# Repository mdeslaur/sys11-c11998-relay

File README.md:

# Williams System 11 24v Relay board

This is a replacement 24v relay board for use in Williams System 11
pinball machines. The original part number is C-11998-1.

It is in KiCad 7 format.

The gerbers for JLCPCB are in the zip file in the gerbers directory.

This has not been tested yet. Version 1.0 of this design will be tested
soon in a Williams Diner.

Change history:  
1.0 - Initial version  

To Do:  
- Clean up the schematic.  

Marc Deslauriers
2024-01-16

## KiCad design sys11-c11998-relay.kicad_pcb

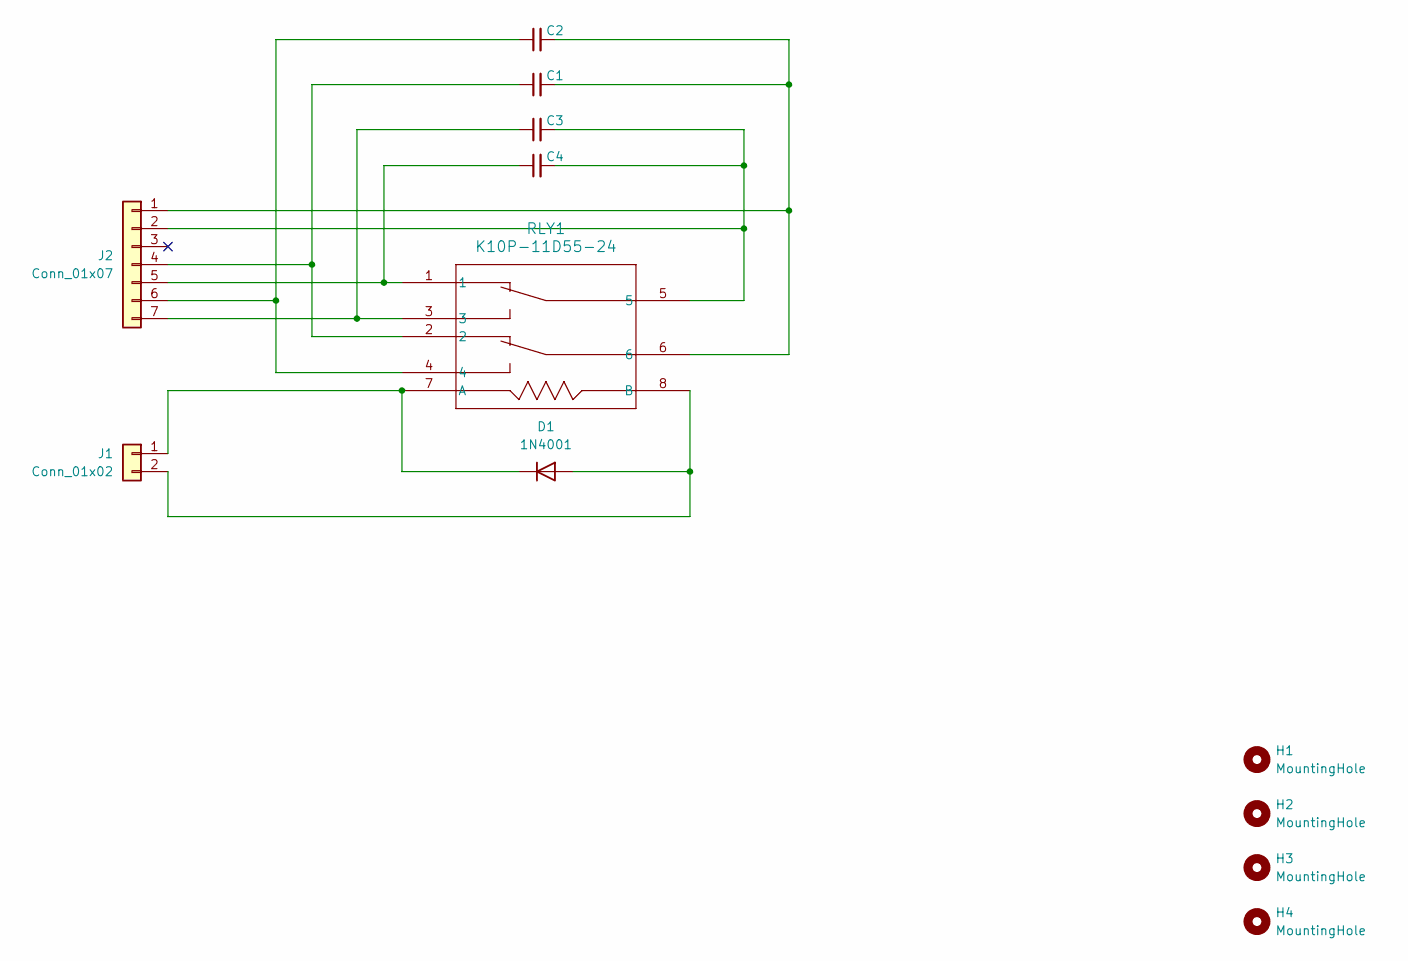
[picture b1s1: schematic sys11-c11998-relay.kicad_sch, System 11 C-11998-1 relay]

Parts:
C1, C2, C3, C4: Unpopulated; C_Axial_L3.8mm_D2.6mm_P10.00mm_Horizontal
D1: 1N4001; D_DO-41_SOD81_P12.70mm_Horizontal
H1, H2, H3, H4: MountingHole; MountingHole_3.2mm_M3
J1: Conn_01x02; Molex_KK-396_5273-02A_1x02_P3.96mm_Vertical_mod
J2: Conn_01x07; Molex_KK-396_5273-07A_1x07_P3.96mm_Vertical_mod
RLY1: K10P-11D55-24

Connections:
unnamed: D1.2 (A), J1.2, RLY1.8 (B)
unnamed: D1.1 (K), J1.1, RLY1.7 (A)
unnamed: C1.2, C2.2, J2.1, RLY1.6
unnamed: C3.2, C4.2, J2.2, RLY1.5
unnamed: C1.1, J2.4, RLY1.2
unnamed: C4.1, J2.5, RLY1.1
unnamed: C2.1, J2.6, RLY1.4
unnamed: C3.1, J2.7, RLY1.3

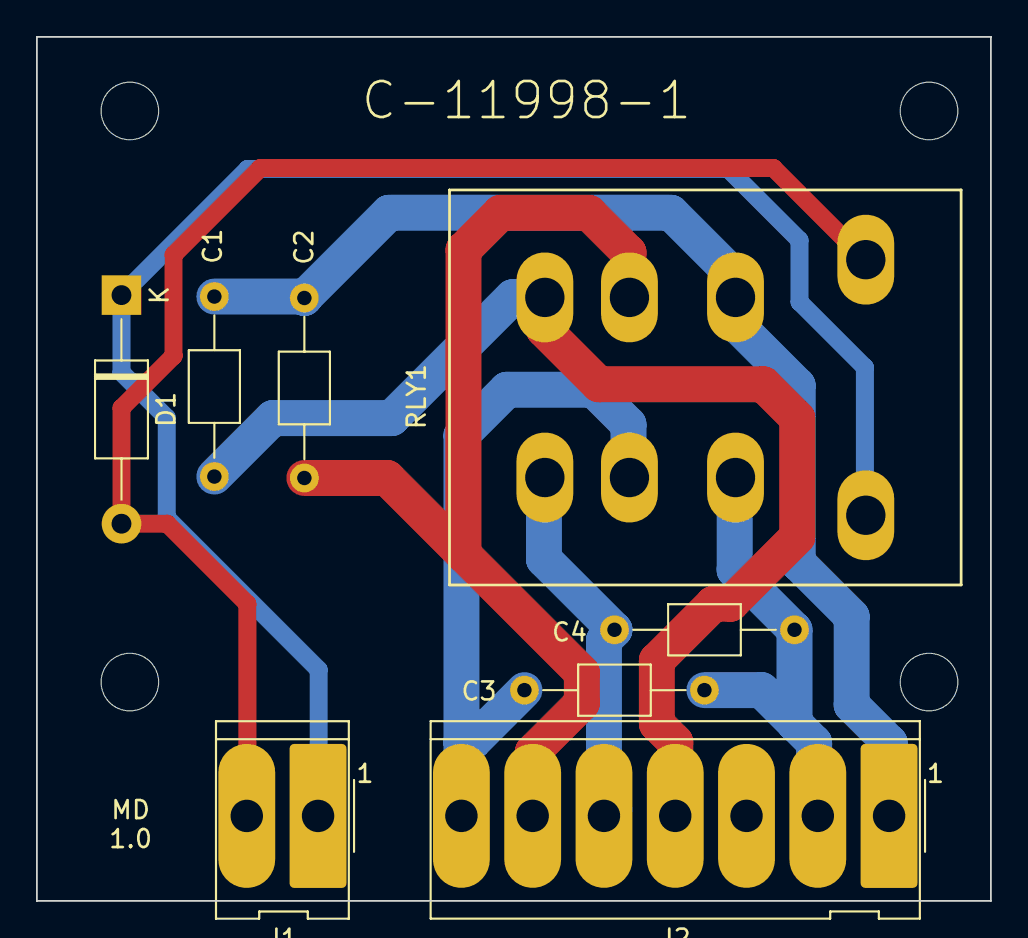
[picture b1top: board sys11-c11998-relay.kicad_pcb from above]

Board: 2 copper layers, 53.0 x 48.0 mm, 12 parts (0 on the bottom side), 8 nets.

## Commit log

2024-01-20 clarified warning in readme file
2024-01-26 README.md: clarify this is in KiCad 7 format
